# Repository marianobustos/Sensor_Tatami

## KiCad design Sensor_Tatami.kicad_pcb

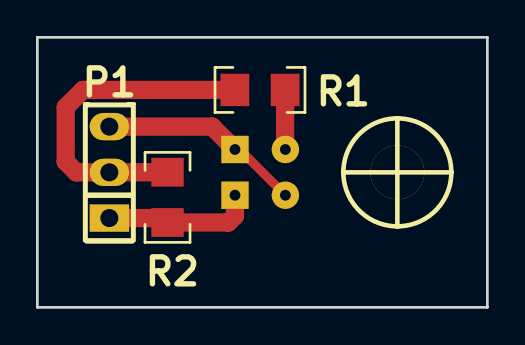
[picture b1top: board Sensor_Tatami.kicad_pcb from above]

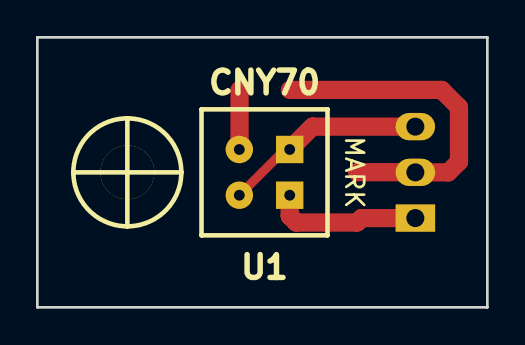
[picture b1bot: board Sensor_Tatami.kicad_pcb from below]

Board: 2 copper layers, 25.0 x 15.0 mm, 5 parts (2 on the bottom side), 4 nets.

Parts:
H1: Mounting_Hole; Tornillo_M3_8mm
P1: CONN_01X03; Pin_Strip_3_90
R1: 220; R_1206
R2: 4K7; R_1206
U1: CNY70

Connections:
/OUT1: P1.1, R2.2, U1.3
GND: P1.3, U1.2, U1.4
unnamed: R1.2, U1.1
VCC: P1.2, R1.1, R2.1

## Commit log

2017-11-22 Versión Inicial
